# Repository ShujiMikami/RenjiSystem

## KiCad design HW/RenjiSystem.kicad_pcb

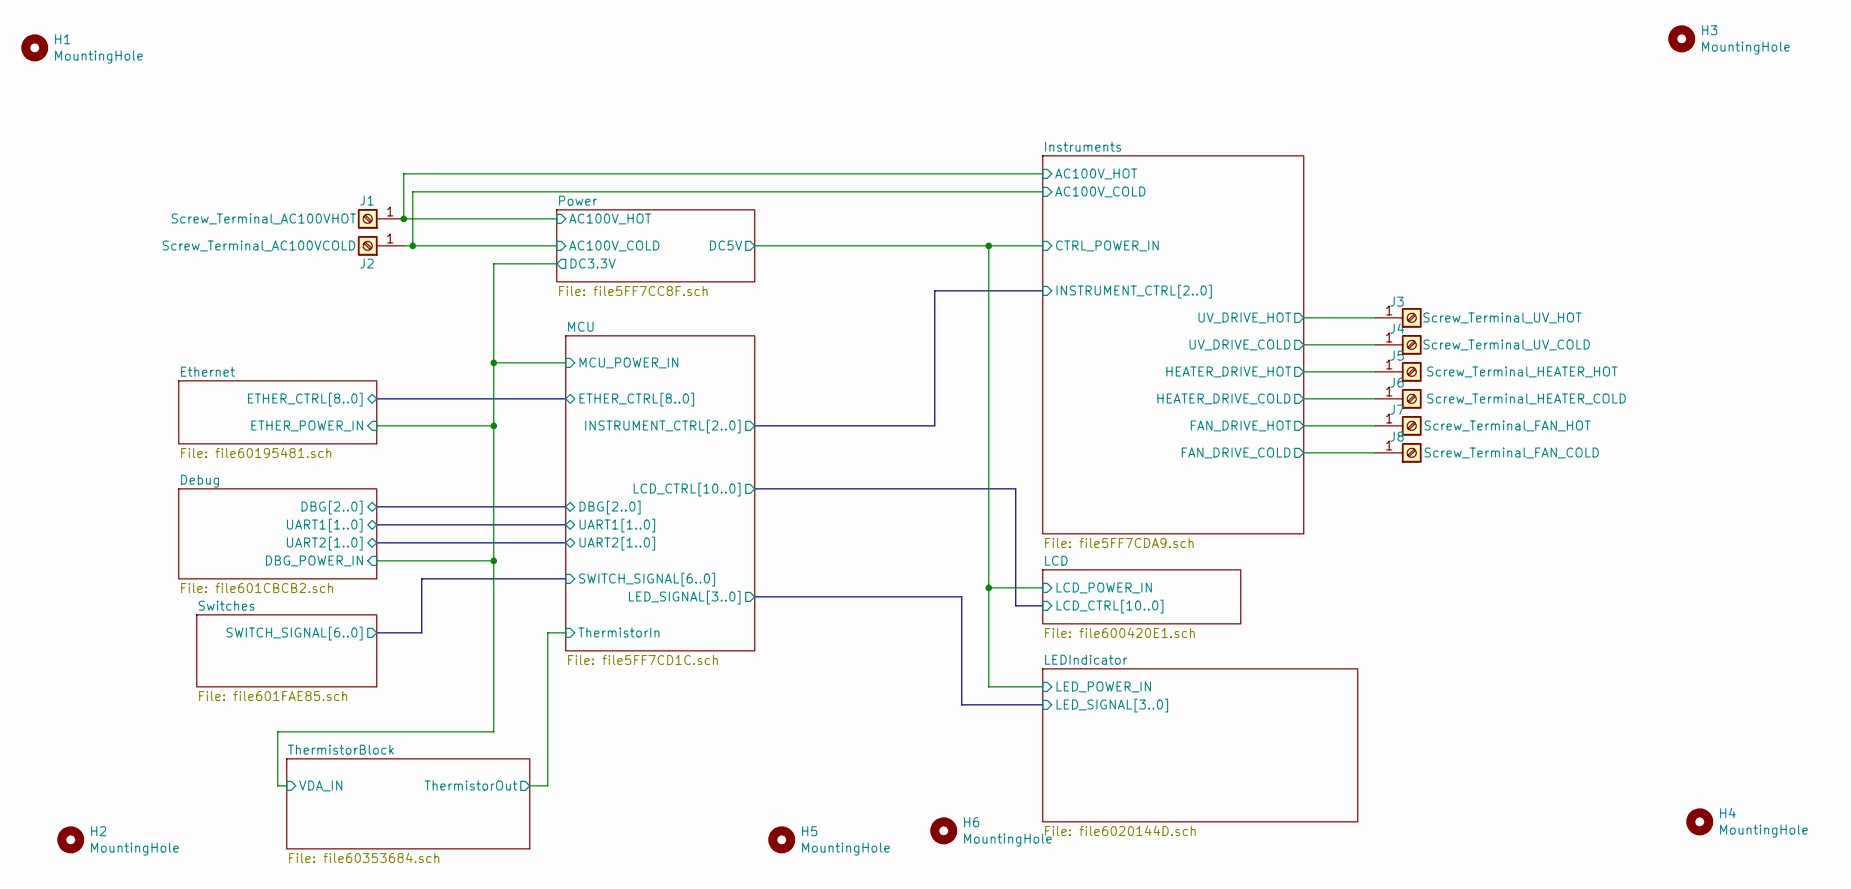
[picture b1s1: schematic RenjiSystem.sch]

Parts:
H1, H2, H3, H4, H5, H6: MountingHole; MountingHole_3.2mm_M3
J1: Screw_Terminal_AC100VHOT; PCB-20(632)F
J2: Screw_Terminal_AC100VCOLD; PCB-20(632)F
J3: Screw_Terminal_UV_HOT; PCB-20(632)F
J4: Screw_Terminal_UV_COLD; PCB-20(632)F
J5: Screw_Terminal_HEATER_HOT; PCB-20(632)F
J6: Screw_Terminal_HEATER_COLD; PCB-20(632)F
J7: Screw_Terminal_FAN_HOT; PCB-20(632)F
J8: Screw_Terminal_FAN_COLD; PCB-20(632)F

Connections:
/Instruments/AC100V_HOT: J1.1; also elsewhere on the board
/Instruments/FAN_DRIVE_HOT: J7.1; also elsewhere on the board
/Instruments/HEATER_DRIVE_HOT: J5.1; also elsewhere on the board
/Instruments/UV_DRIVE_HOT: J3.1; also elsewhere on the board
Earth: J2.1, J4.1, J6.1, J8.1; also elsewhere on the board

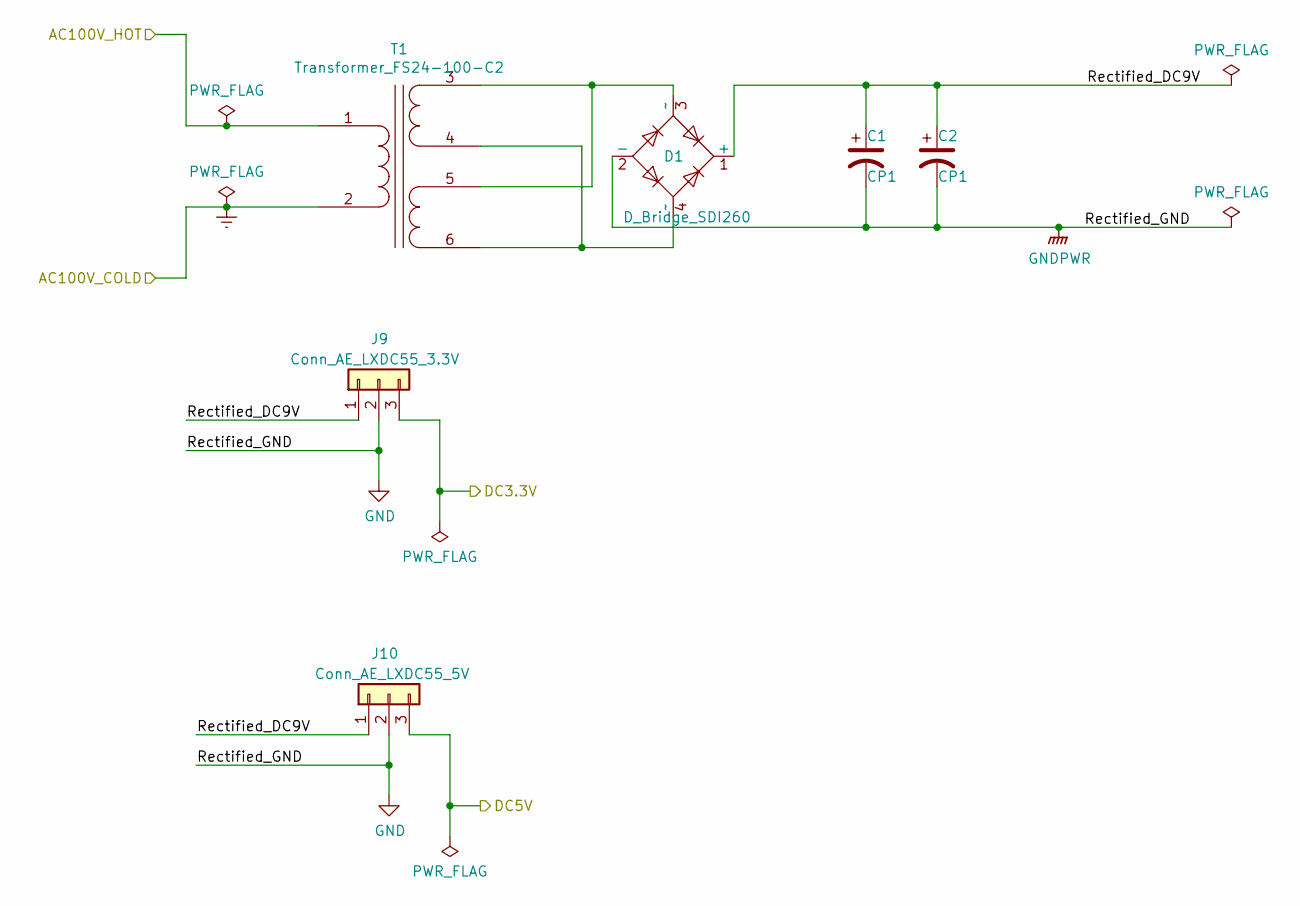
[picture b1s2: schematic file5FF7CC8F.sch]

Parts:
C1, C2: CP1; CP_Radial_D12.5mm_P5.00mm
D1: D_Bridge_SDI260; Diode_Bridge_DIP-4_W7.62mm_P5.08mm
J9: Conn_AE_LXDC55_3.3V; PinSocket_1x03_P2.54mm_Vertical
J10: Conn_AE_LXDC55_5V; PinSocket_1x03_P2.54mm_Vertical
T1: Transformer_FS24-100-C2; F24-250-C2

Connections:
+BATT: J9.3; also elsewhere on the board
/Instruments/AC100V_HOT: T1.1 (AA); also elsewhere on the board
/Instruments/CTRL_POWER_IN: J10.3; also elsewhere on the board
/Power/Rectified_DC9V: C1.1, C2.1, D1.1 (+), J9.1, J10.1
Earth: T1.2 (AB); also elsewhere on the board
GND: C1.2, C2.2, D1.2 (-), J9.2, J10.2; also elsewhere on the board
unnamed: D1.3 (~~), T1.3 (SA), T1.5 (SC)
unnamed: D1.4 (~~), T1.4 (SB), T1.6 (SD)

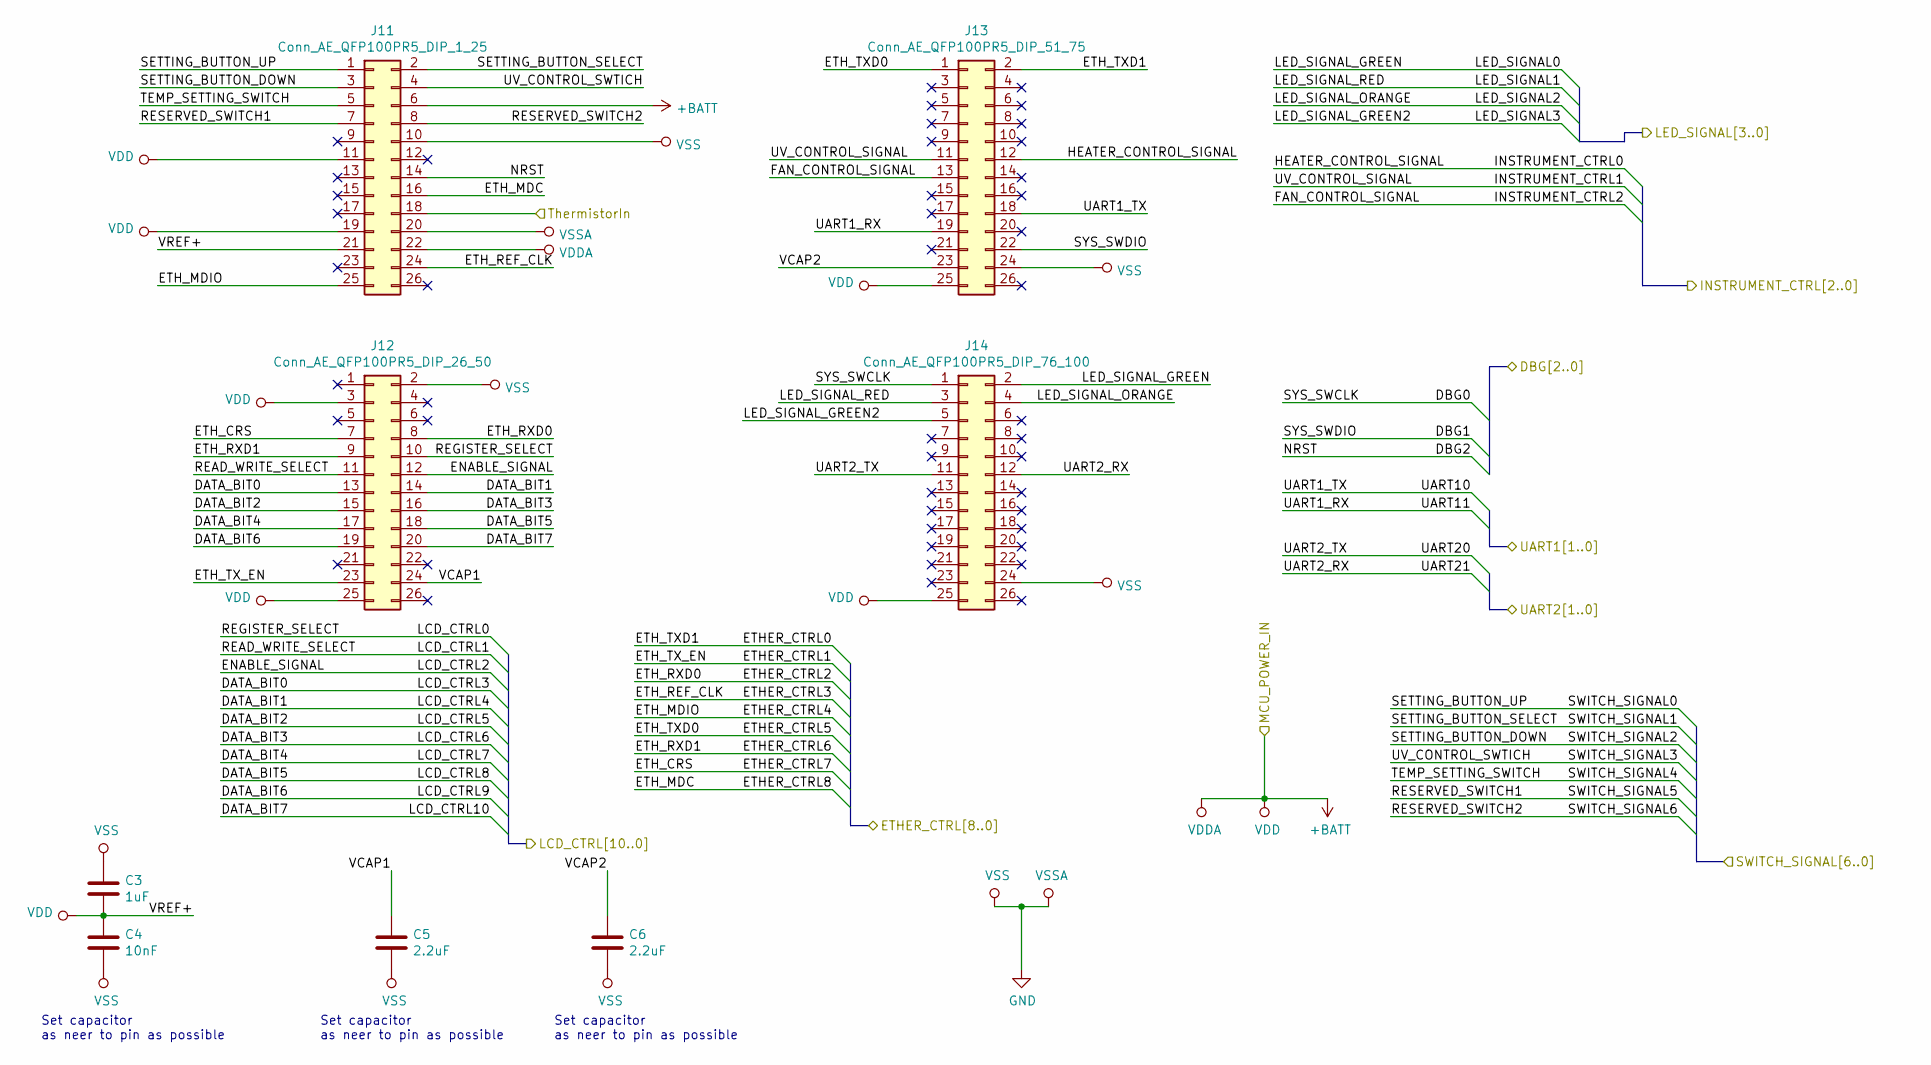
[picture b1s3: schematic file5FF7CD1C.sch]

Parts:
C3: 1uF; C_Rect_L4.0mm_W2.5mm_P2.50mm
C4: 10nF; C_Rect_L4.0mm_W2.5mm_P2.50mm
C5, C6: 2.2uF; C_Rect_L4.0mm_W2.5mm_P2.50mm
J11: Conn_AE_QFP100PR5_DIP_1_25; PinSocket_2x13_P2.54mm_Vertical
J12: Conn_AE_QFP100PR5_DIP_26_50; PinSocket_2x13_P2.54mm_Vertical
J13: Conn_AE_QFP100PR5_DIP_51_75; PinSocket_2x13_P2.54mm_Vertical
J14: Conn_AE_QFP100PR5_DIP_76_100; PinSocket_2x13_P2.54mm_Vertical

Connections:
+BATT: C3.2, C4.1, J11.6, J11.11, J11.19, J11.21, J11.22, J12.3, J12.25, J13.25, J14.25; also elsewhere on the board
/Debug/DBG0: J14.1; also elsewhere on the board
/Debug/DBG1: J13.22; also elsewhere on the board
/Debug/DBG2: J11.14; also elsewhere on the board
/Debug/UART10: J13.18; also elsewhere on the board
/Debug/UART11: J13.19; also elsewhere on the board
/Debug/UART20: J14.11; also elsewhere on the board
/Debug/UART21: J14.12; also elsewhere on the board
/Ethernet/ETHER_CTRL0: J13.2; also elsewhere on the board
/Ethernet/ETHER_CTRL1: J12.23; also elsewhere on the board
/Ethernet/ETHER_CTRL2: J12.8; also elsewhere on the board
/Ethernet/ETHER_CTRL3: J11.24; also elsewhere on the board
/Ethernet/ETHER_CTRL4: J11.25; also elsewhere on the board
/Ethernet/ETHER_CTRL5: J13.1; also elsewhere on the board
/Ethernet/ETHER_CTRL6: J12.9; also elsewhere on the board
/Ethernet/ETHER_CTRL7: J12.7; also elsewhere on the board
/Ethernet/ETHER_CTRL8: J11.16; also elsewhere on the board
/Instruments/FAN_CONTROL_SIGNAL: J13.13; also elsewhere on the board
/Instruments/HEATER_CONTROL_SIGNAL: J13.11; also elsewhere on the board
/LCD/DATA_BIT0: J12.13; also elsewhere on the board
/LCD/DATA_BIT1: J12.14; also elsewhere on the board
/LCD/DATA_BIT2: J12.15; also elsewhere on the board
/LCD/DATA_BIT3: J12.16; also elsewhere on the board
/LCD/DATA_BIT4: J12.17; also elsewhere on the board
/LCD/DATA_BIT5: J12.18; also elsewhere on the board
/LCD/DATA_BIT6: J12.19; also elsewhere on the board
/LCD/DATA_BIT7: J12.20; also elsewhere on the board
/LCD/ENABLE_SIGNAL: J12.12; also elsewhere on the board
/LCD/LCD_CTRL0: J12.10; also elsewhere on the board
/LCD/LCD_CTRL1: J12.11; also elsewhere on the board
/LEDIndicator/LED_SIGNAL0: J14.2; also elsewhere on the board
/LEDIndicator/LED_SIGNAL1: J14.3; also elsewhere on the board
/LEDIndicator/LED_SIGNAL2: J14.4; also elsewhere on the board
/LEDIndicator/LED_SIGNAL3: J14.5; also elsewhere on the board
/MCU/HEATER_CONTROL_SIGNAL: J13.12; also elsewhere on the board
/MCU/RESERVED_SWITCH1: J11.7; also elsewhere on the board
/MCU/RESERVED_SWITCH2: J11.8; also elsewhere on the board
/MCU/SETTING_BUTTON_DOWN: J11.3; also elsewhere on the board
/MCU/SETTING_BUTTON_SELECT: J11.2; also elsewhere on the board
/MCU/SETTING_BUTTON_UP: J11.1; also elsewhere on the board
/MCU/SWITCH_SIGNAL3: J11.4; also elsewhere on the board
/MCU/SWITCH_SIGNAL4: J11.5; also elsewhere on the board
/MCU/ThermistorIn: J11.18; also elsewhere on the board
/MCU/VCAP1: C5.1, J12.24
/MCU/VCAP2: C6.1, J13.23
GND: C3.1, C4.2, C5.2, C6.2, J11.10, J11.20, J12.2, J13.24, J14.24; also elsewhere on the board

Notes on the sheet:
Set capacitor as neer to pin as possible

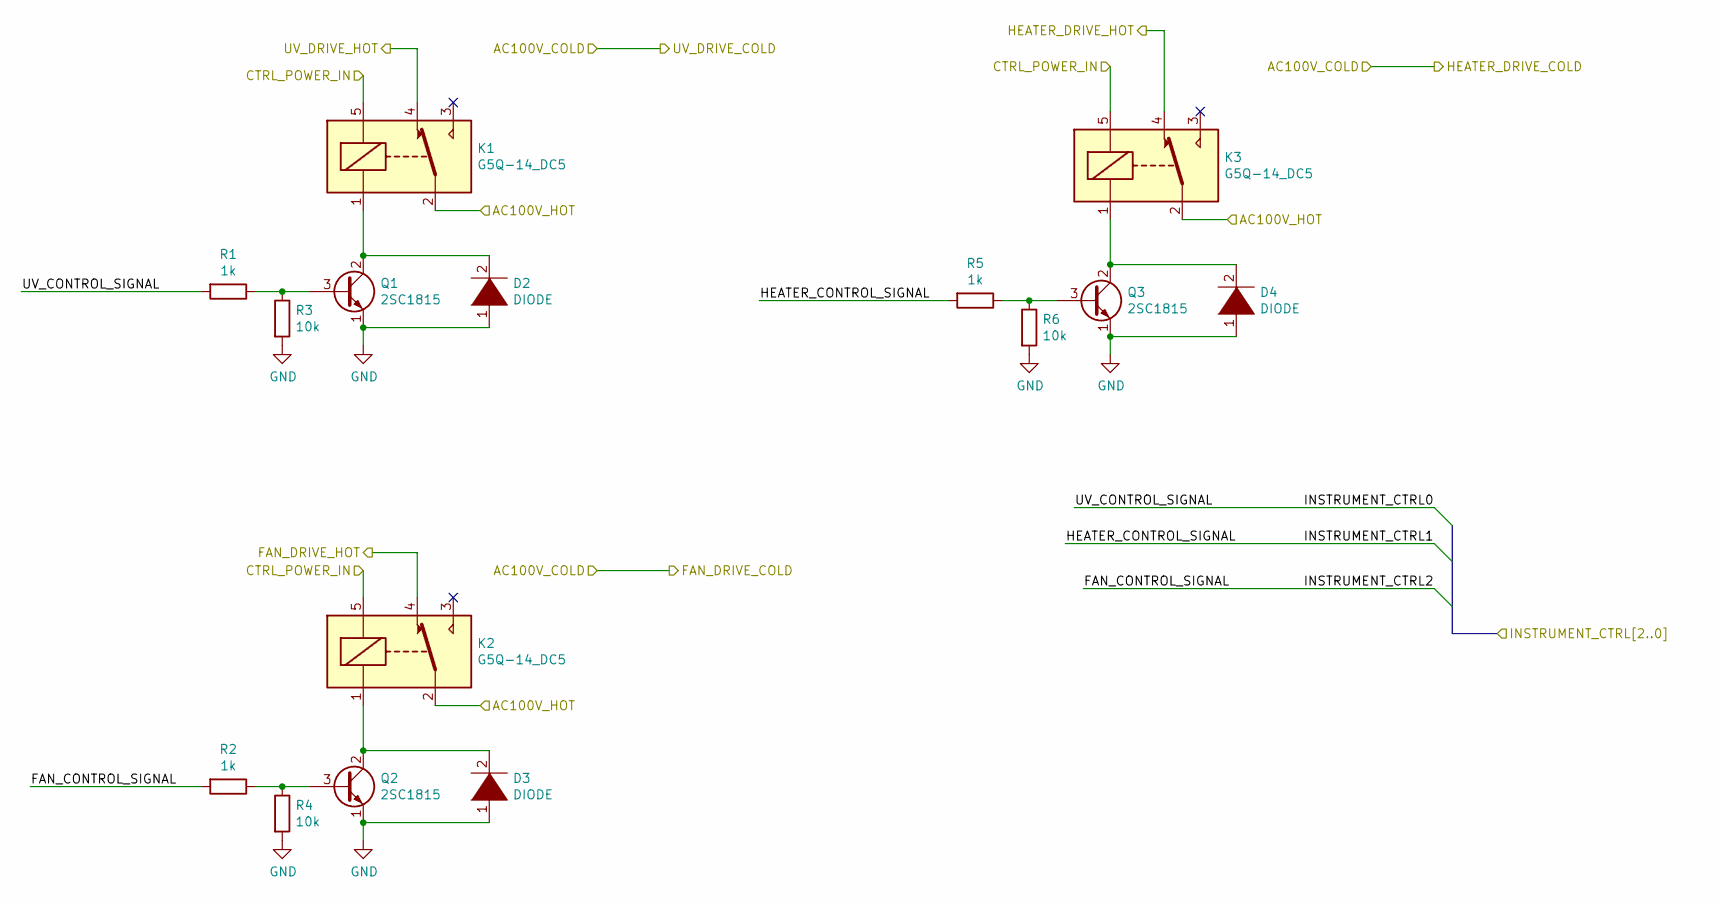
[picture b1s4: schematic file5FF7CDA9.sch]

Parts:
D2, D3, D4: DIODE; D_5W_P5.08mm_Vertical_AnodeUp
K1, K2, K3: G5Q-14_DC5; Relay_SPDT_Omron-G5Q-1
Q1, Q2, Q3: 2SC1815; TO-92_Inline
R1, R2, R5: 1k; R_Axial_DIN0207_L6.3mm_D2.5mm_P7.62mm_Horizontal
R3, R4, R6: 10k; R_Axial_DIN0207_L6.3mm_D2.5mm_P7.62mm_Horizontal

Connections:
/Instruments/AC100V_HOT: K1.2, K2.2, K3.2; also elsewhere on the board
/Instruments/CTRL_POWER_IN: K1.5, K2.5, K3.5; also elsewhere on the board
/Instruments/FAN_CONTROL_SIGNAL: R2.2; also elsewhere on the board
/Instruments/FAN_DRIVE_HOT: K2.3; also elsewhere on the board
/Instruments/HEATER_CONTROL_SIGNAL: R5.2; also elsewhere on the board
/Instruments/HEATER_DRIVE_HOT: K3.3; also elsewhere on the board
/Instruments/UV_DRIVE_HOT: K1.3; also elsewhere on the board
/MCU/HEATER_CONTROL_SIGNAL: R1.2; also elsewhere on the board
GND: D2.1 (K), D3.1 (K), D4.1 (K), Q1.1 (E), Q2.1 (E), Q3.1 (E), R3.2, R4.2, R6.2; also elsewhere on the board
unnamed: D2.2 (A), K1.1, Q1.2 (C)
unnamed: D3.2 (A), K2.1, Q2.2 (C)
unnamed: D4.2 (A), K3.1, Q3.2 (C)
unnamed: Q1.3 (B), R1.1, R3.1
unnamed: Q2.3 (B), R2.1, R4.1
unnamed: Q3.3 (B), R5.1, R6.1

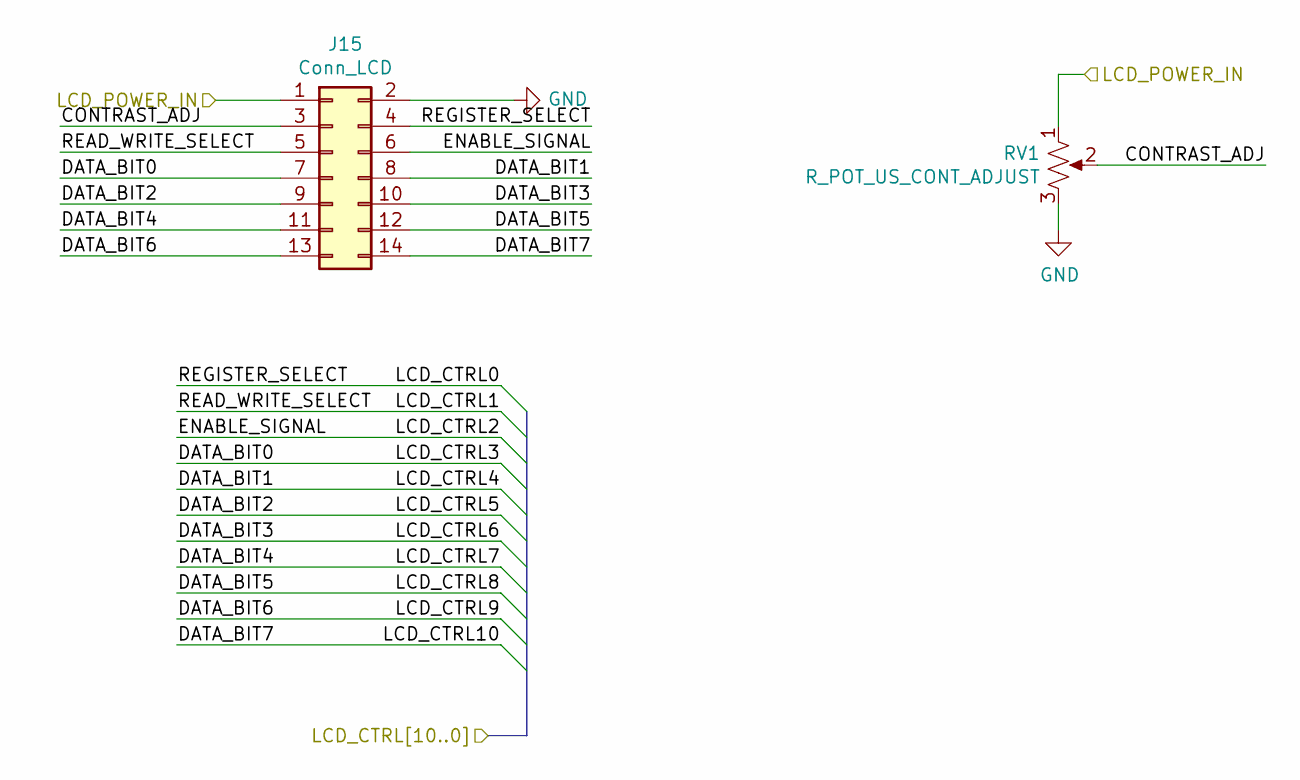
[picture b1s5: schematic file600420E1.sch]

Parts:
J15: Conn_LCD; PinHeader_2x07_P2.54mm_Vertical
RV1: R_POT_US_CONT_ADJUST; Potentiometer_Bourns_3339P_Vertical_HandSoldering

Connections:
/Instruments/CTRL_POWER_IN: J15.1, RV1.1; also elsewhere on the board
/LCD/CONTRAST_ADJ: J15.3, RV1.2
/LCD/DATA_BIT0: J15.7; also elsewhere on the board
/LCD/DATA_BIT1: J15.8; also elsewhere on the board
/LCD/DATA_BIT2: J15.9; also elsewhere on the board
/LCD/DATA_BIT3: J15.10; also elsewhere on the board
/LCD/DATA_BIT4: J15.11; also elsewhere on the board
/LCD/DATA_BIT5: J15.12; also elsewhere on the board
/LCD/DATA_BIT6: J15.13; also elsewhere on the board
/LCD/DATA_BIT7: J15.14; also elsewhere on the board
/LCD/ENABLE_SIGNAL: J15.6; also elsewhere on the board
/LCD/LCD_CTRL0: J15.4; also elsewhere on the board
/LCD/LCD_CTRL1: J15.5; also elsewhere on the board
GND: J15.2, RV1.3; also elsewhere on the board

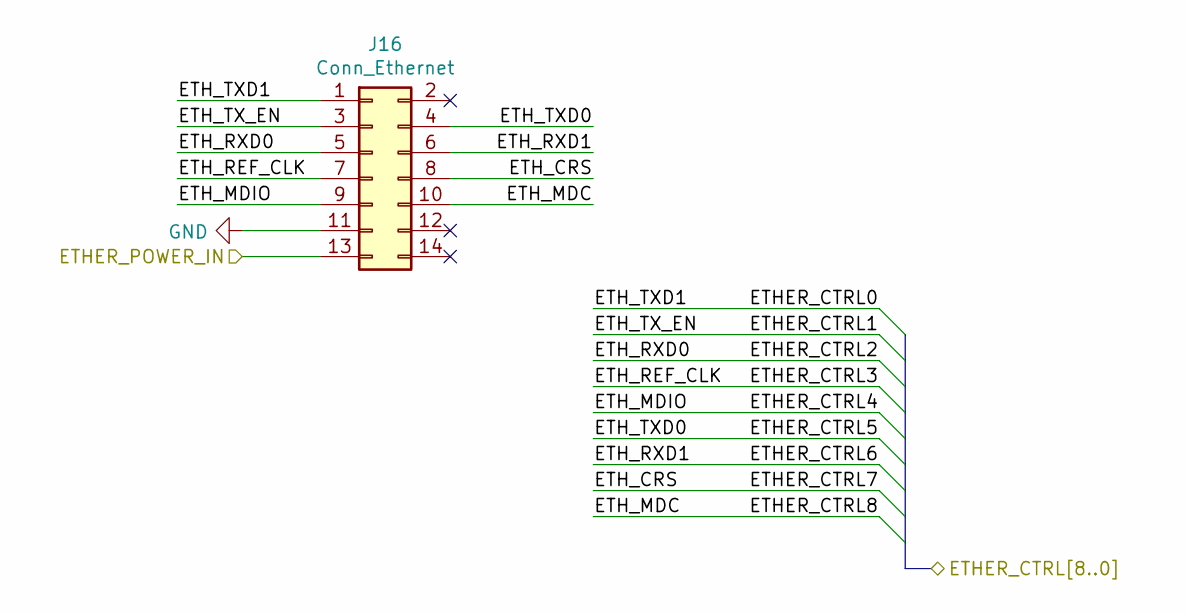
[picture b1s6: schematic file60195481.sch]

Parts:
J16: Conn_Ethernet; PinHeader_2x07_P2.54mm_Vertical

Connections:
+BATT: J16.13; also elsewhere on the board
/Ethernet/ETHER_CTRL0: J16.1; also elsewhere on the board
/Ethernet/ETHER_CTRL1: J16.3; also elsewhere on the board
/Ethernet/ETHER_CTRL2: J16.5; also elsewhere on the board
/Ethernet/ETHER_CTRL3: J16.7; also elsewhere on the board
/Ethernet/ETHER_CTRL4: J16.9; also elsewhere on the board
/Ethernet/ETHER_CTRL5: J16.4; also elsewhere on the board
/Ethernet/ETHER_CTRL6: J16.6; also elsewhere on the board
/Ethernet/ETHER_CTRL7: J16.8; also elsewhere on the board
/Ethernet/ETHER_CTRL8: J16.10; also elsewhere on the board
GND: J16.11; also elsewhere on the board

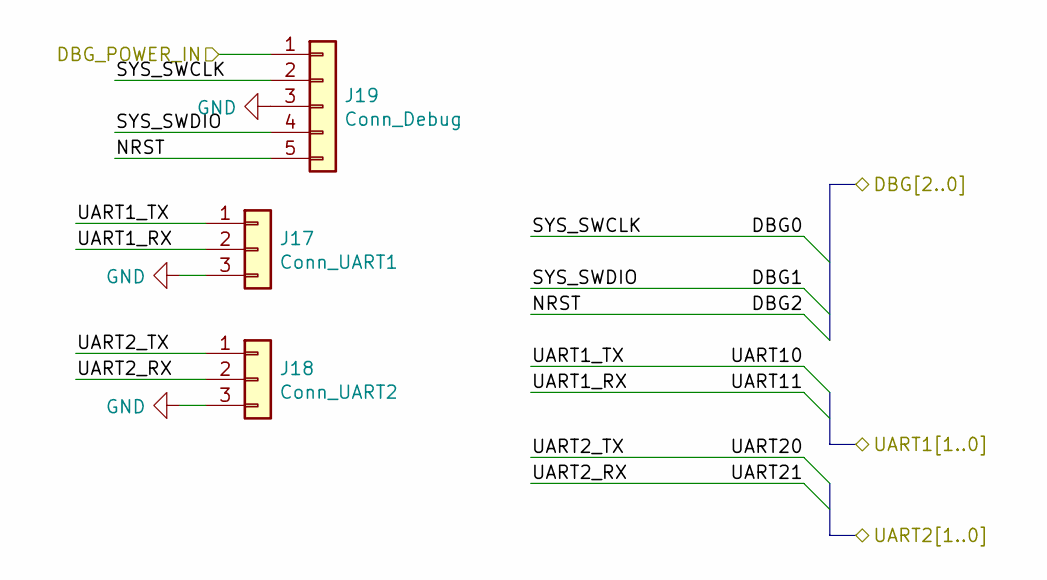
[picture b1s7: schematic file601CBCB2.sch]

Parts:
J17: Conn_UART1; PinHeader_1x03_P2.54mm_Horizontal
J18: Conn_UART2; PinHeader_1x03_P2.54mm_Horizontal
J19: Conn_Debug; PinHeader_1x05_P2.54mm_Horizontal

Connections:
+BATT: J19.1; also elsewhere on the board
/Debug/DBG0: J19.2; also elsewhere on the board
/Debug/DBG1: J19.4; also elsewhere on the board
/Debug/DBG2: J19.5; also elsewhere on the board
/Debug/UART10: J17.1; also elsewhere on the board
/Debug/UART11: J17.2; also elsewhere on the board
/Debug/UART20: J18.1; also elsewhere on the board
/Debug/UART21: J18.2; also elsewhere on the board
GND: J17.3, J18.3, J19.3; also elsewhere on the board

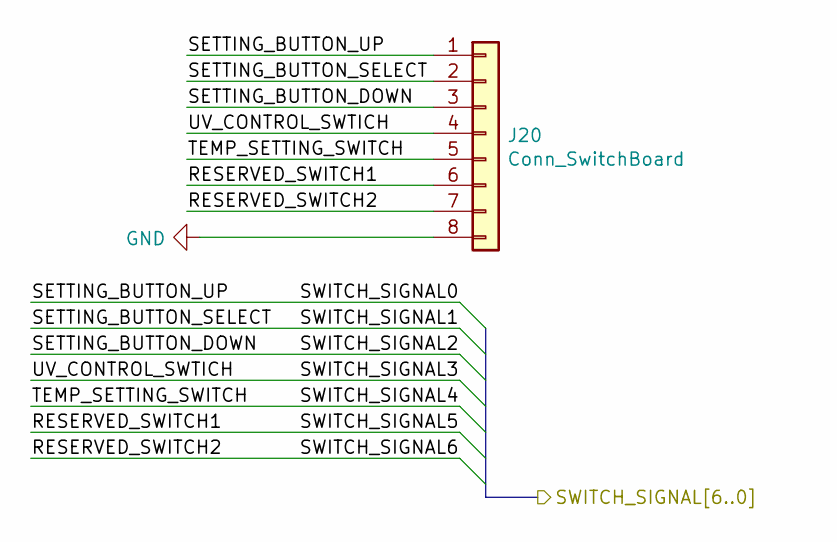
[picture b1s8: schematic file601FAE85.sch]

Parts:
J20: Conn_SwitchBoard; PinSocket_1x08_P2.54mm_Vertical

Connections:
/MCU/RESERVED_SWITCH1: J20.6; also elsewhere on the board
/MCU/RESERVED_SWITCH2: J20.7; also elsewhere on the board
/MCU/SETTING_BUTTON_DOWN: J20.3; also elsewhere on the board
/MCU/SETTING_BUTTON_SELECT: J20.2; also elsewhere on the board
/MCU/SETTING_BUTTON_UP: J20.1; also elsewhere on the board
/MCU/SWITCH_SIGNAL3: J20.4; also elsewhere on the board
/MCU/SWITCH_SIGNAL4: J20.5; also elsewhere on the board
GND: J20.8; also elsewhere on the board

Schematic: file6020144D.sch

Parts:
J21: Conn_LEDIndicator; PinSocket_1x06_P2.54mm_Vertical

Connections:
/Instruments/CTRL_POWER_IN: J21.1; also elsewhere on the board
/LEDIndicator/LED_SIGNAL0: J21.2; also elsewhere on the board
/LEDIndicator/LED_SIGNAL1: J21.3; also elsewhere on the board
/LEDIndicator/LED_SIGNAL2: J21.4; also elsewhere on the board
/LEDIndicator/LED_SIGNAL3: J21.5; also elsewhere on the board
GND: J21.6; also elsewhere on the board

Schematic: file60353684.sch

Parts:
J22: Conn_Thermistor; PinSocket_1x02_P2.54mm_Horizontal
R7: 10k; R_Axial_DIN0207_L6.3mm_D2.5mm_P7.62mm_Horizontal

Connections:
+BATT: J22.1; also elsewhere on the board
/MCU/ThermistorIn: J22.2, R7.2; also elsewhere on the board
GND: R7.1; also elsewhere on the board

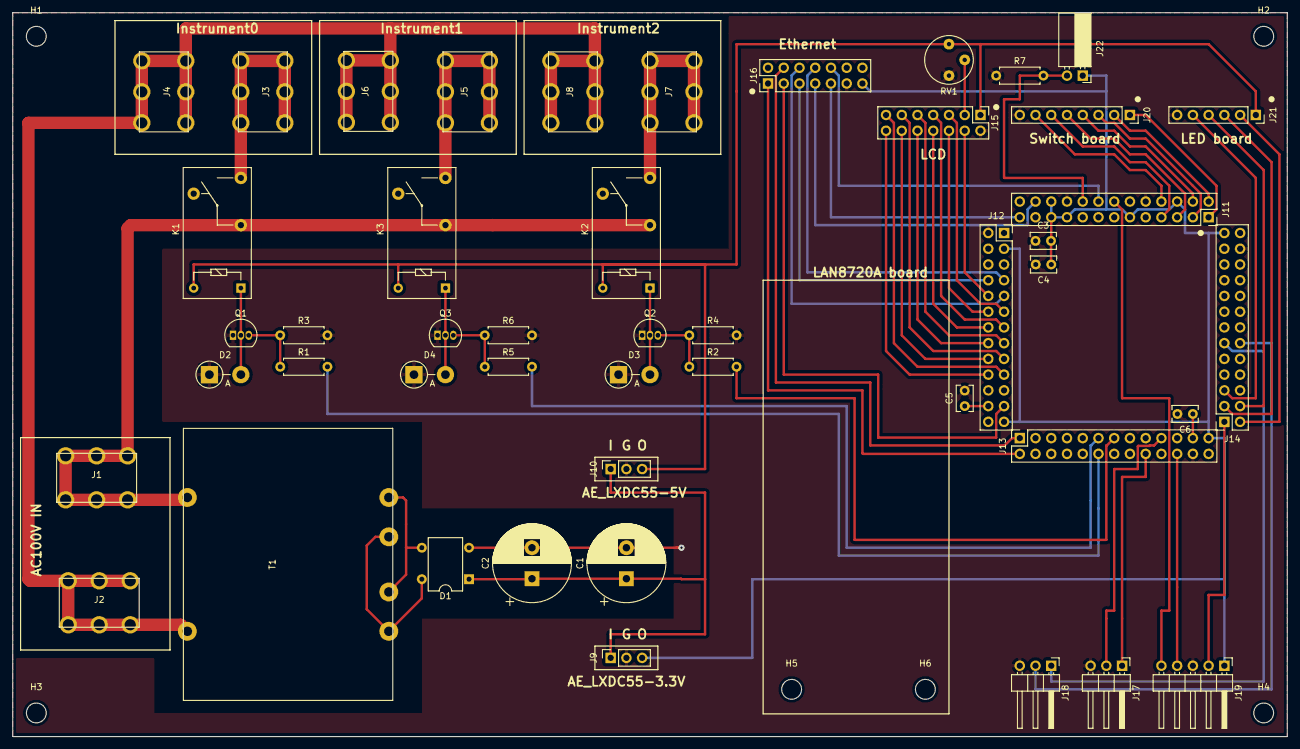
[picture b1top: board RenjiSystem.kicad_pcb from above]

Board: 2 copper layers, 205.7 x 116.8 mm, 53 parts (0 on the bottom side), 62 nets.

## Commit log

2020-12-15 初回, 回路図作成
2020-12-16 フットプリントをトランス以外あてがい
2020-12-16 トランスのフットプリントライブラリ作成
2020-12-16 基板上部品配置
2020-12-16 電源部配線
2020-12-28 ボード回路図を, シート分割
2020-12-28 回路図の配置を修正
2020-12-30 Ethernetボードの配置のためにレイアウト変更
2020-12-31 サーミスタの端子を追記
2020-12-31 シルクで1ピンマーク追記
